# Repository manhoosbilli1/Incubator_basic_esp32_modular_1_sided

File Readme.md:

# V#1.3 Incubator pcb for a client.

contains:
- esp32, 
- wifi and bluetooth capability. 
- works with mobile app
- lcd and encoder for menu navigation
- heater AC PWM and on/off support
- motor AC continuous and limit switch capability 
- fan
- humidifer
- aht20 (i2c Temp/humidity sensor)
- alternate connector for limit switches x2
- alternate connector heater pwm external ssr
- supposed to be delivered in a box with AC=DC convertor, jack, connection points board to box.
- App will be released soon that will report sensor data using firebase.

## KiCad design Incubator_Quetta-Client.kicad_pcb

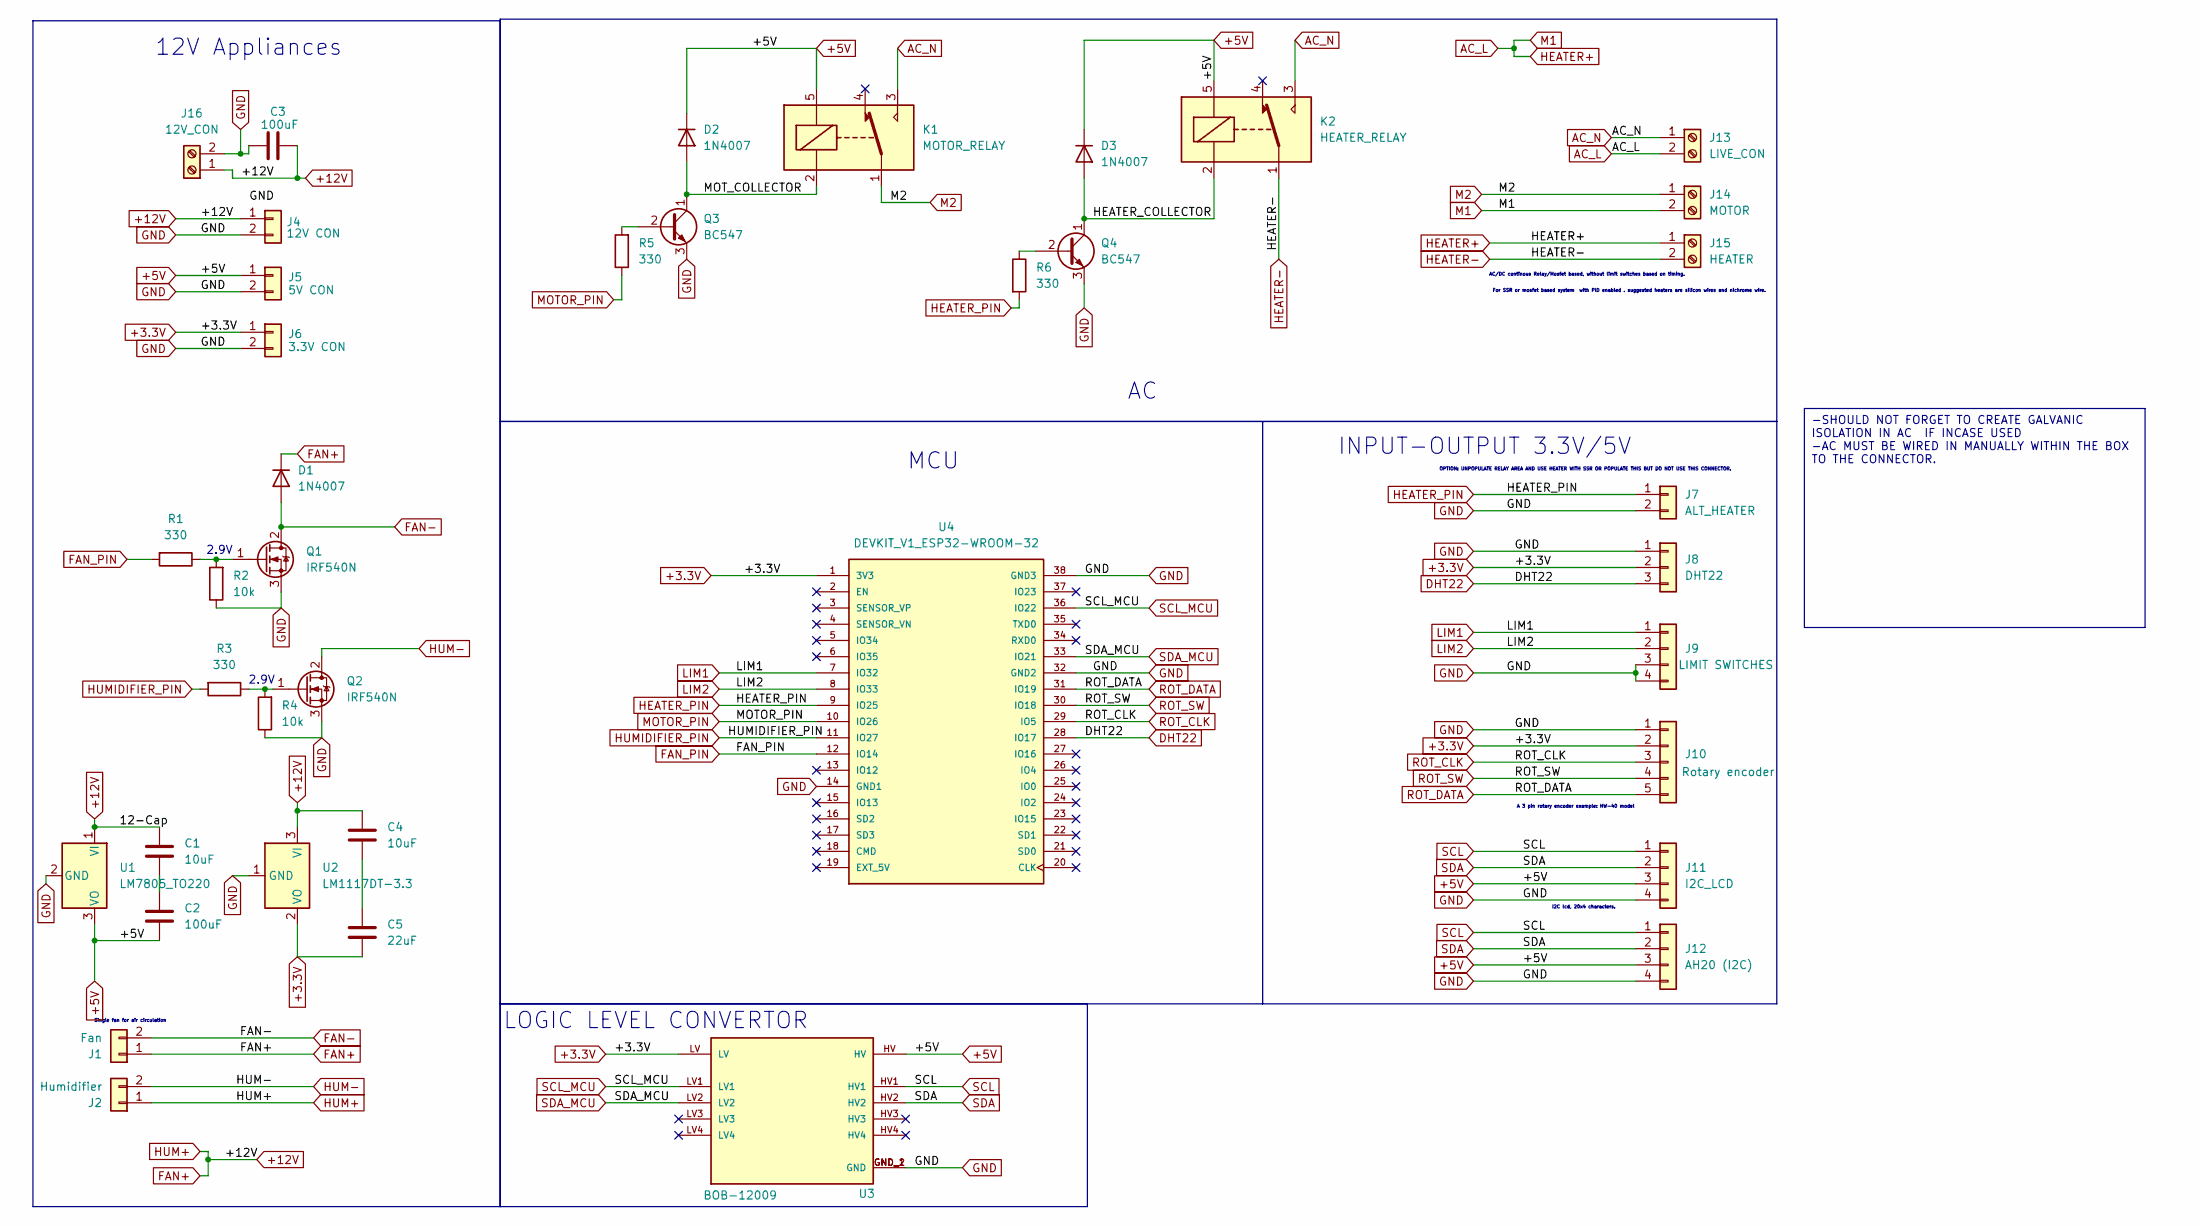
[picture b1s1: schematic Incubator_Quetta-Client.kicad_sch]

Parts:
C1, C4: 10uF; C_Disc_D3.0mm_W1.6mm_P2.50mm
C2: 100uF; C_Disc_D3.0mm_W1.6mm_P2.50mm
C3: 100uF; C_Radial_D6.3mm_H5.0mm_P2.50mm
C5: 22uF; C_Disc_D3.0mm_W1.6mm_P2.50mm
D1, D2, D3: 1N4007; D_DO-41_SOD81_P10.16mm_Horizontal
J1: Fan; PinHeader_1x02_P2.54mm_Horizontal
J2: Humidifier; PinHeader_1x02_P2.54mm_Horizontal
J4: 12V CON; PinHeader_1x02_P2.54mm_Vertical
J5: 5V CON; PinHeader_1x02_P2.54mm_Vertical
J6: 3.3V CON; PinHeader_1x02_P2.54mm_Vertical
J7: ALT_HEATER; PinHeader_1x02_P2.54mm_Vertical
J8: DHT22; PinHeader_1x03_P2.54mm_Vertical
J9: LIMIT SWITCHES; PinHeader_1x04_P2.54mm_Vertical
J10: Rotary encoder; PinHeader_1x05_P2.54mm_Vertical
J11: I2C_LCD; PinHeader_1x04_P2.54mm_Vertical
J12: AH20 (I2C); PinHeader_1x04_P2.54mm_Vertical
J13: LIVE_CON; Altech_AK100_1x02_P5.00mm
J14: MOTOR; Altech_AK100_1x02_P5.00mm
J15: HEATER; Altech_AK100_1x02_P5.00mm
J16: 12V_CON; Altech_AK100_1x02_P5.00mm
K1: MOTOR_RELAY; Relay_SPDT_SANYOU_SRD_Series_Form_C
K2: HEATER_RELAY; Relay_SPDT_SANYOU_SRD_Series_Form_C
Q1, Q2: IRF540N; TO-220-3_Vertical
Q3, Q4: BC547; TO-92_Inline
R1, R6: 330; R_Axial_DIN0204_L3.6mm_D1.6mm_P5.08mm_Horizontal
R2, R4: 10k; PinHeader_1x04_P2.54mm_Vertical
R3, R5: 330; PinHeader_1x04_P2.54mm_Vertical
U1: LM7805_TO220; TO-220-3_Vertical
U2: LM1117DT-3.3; TO-252-3_TabPin2
U3: BOB-12009; CONV_BOB-12009; PARTREV 01
U4: DEVKIT_V1_ESP32-WROOM-32; MODULE_ESP32_DEVKIT_V1; PARTREV N/A

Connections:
+3.3V: C5.2, J6.1, J8.2, J10.2, U2.2 (VO), U3.LV, U4.1 (3V3)
+5V: C2.2, D2.1 (K), D3.1 (K), J5.1, J11.3, J12.3, K1.5, K2.5, U1.3 (VO), U3.HV
+12V: C1.1, C3.2, C4.1, D1.1 (K), J1.1, J2.1, J4.1, J16.1, U1.1 (VI), U2.3 (VI)
/HEATER_COLLECTOR: D3.2 (A), K2.2, Q4.1 (C)
/MOT_COLLECTOR: D2.2 (A), K1.2, Q3.1 (C)
AC_L: J13.2, J14.2, J15.1
AC_N: J13.1, K1.3, K2.3
DHT22: J8.3, U4.28 (IO17)
FAN-: D1.2 (A), J1.2, Q1.2 (D)
FAN_PIN: R1.2, U4.12 (IO14)
GND: C3.1, J4.2, J5.2, J6.2, J7.2, J8.1, J9.3, J9.4, J10.1, J11.4, J12.4, J16.2, Q1.3 (S), Q2.3 (S), Q3.3 (E), Q4.3 (E), R2.1, R4.1, U1.2 (GND), U2.1 (GND), U3.GND_1 (GND), U3.GND_2 (GND), U4.14 (GND1), U4.32 (GND2), U4.38 (GND3)
HEATER-: J15.2, K2.1
HEATER_PIN: J7.1, R6.2, U4.9 (IO25)
HUM-: J2.2, Q2.2 (D)
HUMIDIFIER_PIN: R3.2, U4.11 (IO27)
LIM1: J9.1, U4.7 (IO32)
LIM2: J9.2, U4.8 (IO33)
M2: J14.1, K1.1
MOTOR_PIN: R5.1, U4.10 (IO26)
unnamed: C1.2, C2.1
unnamed: C4.2, C5.1
unnamed: Q1.1 (G), R1.1, R2.2
unnamed: Q2.1 (G), R3.1, R4.2
unnamed: Q3.2 (B), R5.2
unnamed: Q4.2 (B), R6.1
ROT_CLK: J10.3, U4.29 (IO5)
ROT_DATA: J10.5, U4.31 (IO19)
ROT_SW: J10.4, U4.30 (IO18)
SCL: J11.1, J12.1, U3.HV1
SCL_MCU: U3.LV1, U4.36 (IO22)
SDA: J11.2, J12.2, U3.HV2
SDA_MCU: U3.LV2, U4.33 (IO21)

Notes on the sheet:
-SHOULD NOT FORGET TO CREATE GALVANIC ISOLATION IN AC IF INCASE USED -AC MUST BE WIRED IN MANUALLY WITHIN THE BOX TO THE CONNECTOR.
I2C lcd, 20x4 characters.
AC/DC continous Relay/Mosfet based, without limit switches based on timing.
MCU
For SSR or mosfet based system with PID enabled . suggested heaters are silicon wires and nichrome wire.
OPTION: UNPOPULATE RELAY AREA AND USE HEATER WITH SSR OR POPULATE THIS BUT DO NOT USE THIS CONNECTOR.
INPUT-OUTPUT 3.3V/5V
12V Appliances
2.9V
LOGIC LEVEL CONVERTOR
A 3 pin rotary encoder example: HW-40 model
Single fan for air circulation

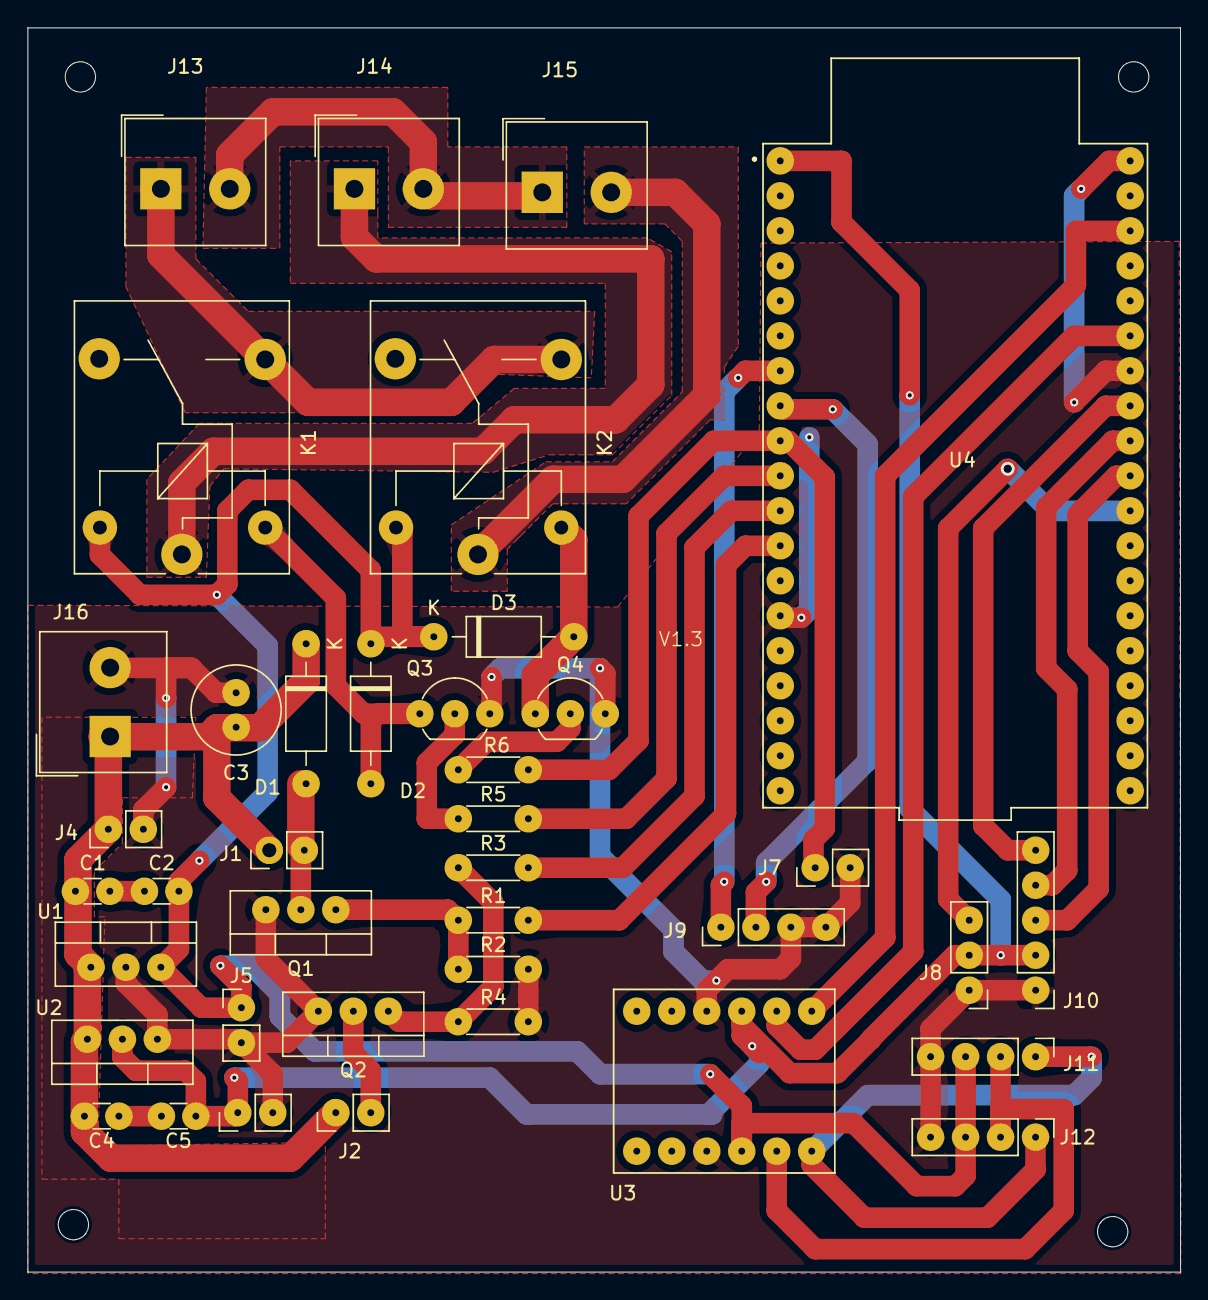
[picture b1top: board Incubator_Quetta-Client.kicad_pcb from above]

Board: 2 copper layers, 83.7 x 90.3 mm, 39 parts (0 on the bottom side), 32 nets.

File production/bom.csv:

Designator,Footprint,Quantity,Value,LCSC Part #
"C1, C4",C_Disc_D3.0mm_W1.6mm_P2.50mm,2,10uF,
C2,C_Disc_D3.0mm_W1.6mm_P2.50mm,1,100uF,
C3,C_Radial_D6.3mm_H5.0mm_P2.50mm,1,100uF,
C5,C_Disc_D3.0mm_W1.6mm_P2.50mm,1,22uF,
"D1, D2, D3",D_DO-41_SOD81_P10.16mm_Horizontal,3,1N4007,
J1,PinHeader_1x02_P2.54mm_Vertical,1,Fan,
J10,PinHeader_1x05_P2.54mm_Vertical,1,Rotary encoder,
J11,PinHeader_1x04_P2.54mm_Vertical,1,I2C_LCD,
J12,PinHeader_1x04_P2.54mm_Vertical,1,AH20 (I2C),
J13,Altech_AK100_1x02_P5.00mm,1,LIVE_CON,
J14,Altech_AK100_1x02_P5.00mm,1,MOTOR,
J15,Altech_AK100_1x02_P5.00mm,1,HEATER,
J16,Altech_AK100_1x02_P5.00mm,1,12V_CON,
J2,PinHeader_1x02_P2.54mm_Vertical,1,Humidifier,
J4,PinHeader_1x02_P2.54mm_Vertical,1,12V CON,
J5,PinHeader_1x02_P2.54mm_Vertical,1,5V CON ,
J6,PinHeader_1x02_P2.54mm_Vertical,1,3.3V CON,
J7,PinHeader_1x02_P2.54mm_Vertical,1,ALT_HEATER,
J8,PinHeader_1x03_P2.54mm_Vertical,1,DHT22,
J9,PinHeader_1x04_P2.54mm_Vertical,1,LIMIT SWITCHES  ,
K1,Relay_SPDT_SANYOU_SRD_Series_Form_C,1,MOTOR_RELAY,
K2,Relay_SPDT_SANYOU_SRD_Series_Form_C,1,HEATER_RELAY,
"Q1, Q2",TO-220-3_Vertical,2,IRF540N,
"Q3, Q4",TO-92_Inline_Wide,2,BC547,
"R1, R3, R5, R6",R_Axial_DIN0204_L3.6mm_D1.6mm_P5.08mm_Horizontal,4,330,
"R2, R4",R_Axial_DIN0204_L3.6mm_D1.6mm_P5.08mm_Horizontal,2,10k,
U1,TO-220-3_Vertical,1,LM7805,
U2,TO-220-3_Vertical,1,LM1117DT-3.3,
U3,CONV_BOB-12009,1,BOB-12009,
U4,MODULE_DEVKIT_V1_ESP32-WROOM-32,1,DEVKIT_V1_ESP32-WROOM-32,

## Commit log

2024-07-02 basic schematic complete
2024-07-03 basic layout done
2024-07-04 finalised pcb. all done. waiting for approval
2024-07-04 added neat pictures to readme
2024-07-04 fixed image not working
2024-07-13 final
